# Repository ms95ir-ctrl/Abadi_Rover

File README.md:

# Abadi Rover

Two robots, one shared motherboard. Each robot has its own files, so they do not get mixed up.

| | Robot | Where its files are | Status |
|---|---|---|---|
| **Abadi Rover 1** | The tracked rover: ELEGOO tracked chassis, Raspberry Pi 5, ESP32-S3 motherboard, camera, audio. | The files at the **top level** of this repository: [`plan.md`](plan.md) (the locked build plan), [`wiring.md`](wiring.md), [`HANDOVER.md`](HANDOVER.md), [`wiring-map.png`](wiring-map.png), [`wiring-map.svg`](wiring-map.svg), [`wiring-map-unoq.png`](wiring-map-unoq.png), [`relay-wiring.png`](relay-wiring.png), [`relay-wiring.svg`](relay-wiring.svg) | In progress (still being built) |
| **Abadi Rover 2** | The telepresence robot: round base, 7 inch screen and camera on a pan/tilt head, Raspberry Pi 5 for video calls. It will be built abroad, so the owner can call family and drive the robot around the house from Germany. | The folder [`abadi-rover-2/`](abadi-rover-2/) (start with its [`README.md`](abadi-rover-2/README.md)) | First design draft |
| **Shared motherboard** | The 100 x 100 mm ESP32-S3 board (KiCad 7, 2 layers) used by both robots. The owner reports that five boards were ordered, for five different robots. | The folder [`pcb/kicad/`](pcb/kicad/) (start with its [`README.md`](pcb/kicad/README.md); locked pin table: [`pin-table.md`](pcb/kicad/pin-table.md)) | v5 designed and checked. Order only after the paper test-fit in `pcb/kicad/README.md` passes. If the owner has already ordered, he must confirm the ordered files are v5 (they must match `pin-table.md`) |

## Rules that keep the two robots apart

- Robot 1's files stay where they are. Other tools (for example Cursor) read `plan.md` at the top level, so they are not moved.
- Robot 2 is written only inside `abadi-rover-2/`. It does not change `plan.md`, `wiring.md`, `HANDOVER.md` or anything else of robot 1.
- The motherboard folder is shared. Its pin table and power design are **locked**; a change needs the owner's explicit approval, because both robots depend on it.
- One stage at a time. A robot's code is only written for the stage that is being built and tested.

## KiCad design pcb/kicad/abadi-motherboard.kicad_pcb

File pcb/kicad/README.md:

# Robot motherboard - routed draft v5, 2 layers, 100 x 100 mm

**Status: DRAFT. Do not order yet.** v5 is built from the owner's paper test-fits, photos and readings of the real modules. It is fully
routed and passes every check I could run on the files. Before ordering: print the new template, check the two DRV8833 modules
and a screen cable against it (see "Still to confirm"), and read the independent-review notes below.

## What changed in v5

- **DRV8833 (HW-627) footprints redrawn: two rows of 6 holes**, as read from the real module. Top row, left to right: IN1 IN2 VCC GND IN3 IN4
  (VCC is the motor supply = the battery). Bottom row, the side with the white plug: EEP OUT1 OUT2 OUT3 OUT4 ULT (EEP and ULT are not used).
  The pin names are printed beside the holes. M1 = DRV A OUT1+OUT2, M2 = DRV A OUT3+OUT4, M3/M4 = the same for DRV B.
  Note: the owner's own wording listed the IN row as "IN4 IN3 GND VCC IN2 IN1"; I drew it in the opposite direction (IN1 IN2 VCC GND IN3 IN4),
  assuming each row was read upright from its own edge, which also matches the seller's pin table. A thick silkscreen bar marks the plug side.
- **Screen headers follow the screens' own order:** CS DC RST SDA SCL VCC GND (pin 1 = square pad = CS).
- **Capacitor ratings are printed on the board** (C1 470uF 16V, C2 100uF 10V, C3/C4 100n) and listed in `parts-list.md`.
- **Plotted board size is exactly 100.0 x 100.0 mm** (the outline line used to add 0.1 mm). The fab cuts along the middle of that 0.1 mm line, so the finished board is
  99.9 x 99.9 mm; the mounting holes do not move. This keeps it inside the cheapest price tier.
- **30 ground stitching vias** tie the top and bottom ground pours together (the farthest spot from a tie is now about 12 mm instead of 37 mm).
- The relay/sonar and I2C/UART header strips have 3.0 mm between neighbouring headers (the screen and SPARE strip at the top is tighter: use slim plugs there),
  the labels on the top header row moved away from the pads and the board edge, version text says v5.
- New files: `shopping-list.md` (everything to buy, including the parts that are not on the board) and `stitch_ground.py`.

Carried over from v4: four 5.08 mm left-edge screw terminals (SERVO 5V IN, BATT IN, CLEAN 5V IN, 3.3V IN), the POWER OUT header
(2 x clean 5 V, 2 x 3.3 V from the 3.3 V buck, 4 x GND), 2-pin JST-style motor spots M1-M4, no series resistors on the relay inputs
(3 V relay modules have their own input circuit), sonar echo dividers 1k/2k (ESP32-S3 pins are not 5 V tolerant).

## How to wire the power

The three bucks are separate modules (not on the board). Each one has an input pair (IN+ / IN-) and an output pair (OUT+ / OUT-).

```
battery pack -> BMS -> main switch -> splice (lever connectors, one for + and one for -; 6-way if the Pi buck is used), one FUSE per branch:
     |-> board terminal BATT IN        (motors; 5 A slow-blow, 6 A at most: the board's 2 mm battery copper is a roughly 6 A design)
     |-> servo buck IN+/IN-  (5 A fuse)  its OUT+/OUT- go to the board terminal SERVO 5V IN   (-> PCA9685 V+ pin)
     |-> clean 5V buck IN+/IN-  (2 A fuse)  its OUT+/OUT- go to the board terminal CLEAN 5V IN   (-> ESP32 5V pin via diode D1, both sonars, POWER OUT 5V pins)
     |-> 3.3V buck IN+/IN-  (2 A fuse)   its OUT+/OUT- go to the board terminal 3.3V IN       (-> relays, screens, POWER OUT 3V3 pins)
     '-> (optional) Raspberry Pi 5: own 5.1 V buck, 5 A fuse, straight to the Pi. It does not touch the board.
```

**+** is the square pad of each terminal. All **-** terminals and all GND pins are one common ground. Before connecting a buck to the board,
power it from the battery alone and set its output with a multimeter (servo buck 5.0 V, clean buck 5.0 V, 3.3 V buck 3.3 V).
The board has no fuse and no reverse-polarity protection. Each POWER OUT rail (two pins) shares one 0.5 mm track: the copper is good for about 2 A,
but the buck also feeds the ESP32, sonars, relays and screens, so plan on about **1 A** for your own sensors. Do not connect one sensor to both the
POWER OUT 3V3 pins (3.3 V buck) and the I2C / SPARE 3V3 pins (the ESP32's own pin): they are different sources. The ESP32
reaches 5 V through D1 and its own diode, so check on first power-up that its 3.3 V pin stays at 3.2 V or higher with Wi-Fi transmitting.

## What is here

| File | What it is |
|---|---|
| `board-top.png` | what the finished board will look like from above |
| `board-copper.png` | both copper layers |
| `fit-template-1to1.pdf` | **print at 100 % / actual size** and lay your modules on it (the 50 mm ruler must measure 50 mm) |
| `abadi-motherboard.kicad_pcb` + `.kicad_pro` | the board in KiCad 7 (keep both files together: the .kicad_pro holds the design rules) |
| `gerber/` and `abadi-motherboard-2layer-gerber.zip` | the fab files (this zip is what you upload to the PCB maker) |
| `pin-table.md` | which ESP32 pin carries which signal, and every connector's pin order |
| `parts-list.md` | what to buy for every footprint, with ratings |
| `shopping-list.md` | everything to buy, on and off the board, plus the first power-up steps |
| `power-wiring.png` / `.svg` | wiring diagram: cells, BMS, charger, splice, fuses, bucks, motherboard terminals |
| `battery-wiring.png` / `.svg` | wiring diagram for the battery only: 2 cells, the BMS (P+ P- / B+ BM B-) and the IP2326 USB-C charger board |
| `reports/` | KiCad's design-rule report and my independent check of the Gerber files |

## Still to confirm (paper test-fit with the new template)

1. **DRV8833 row gap.** The two rows of holes are drawn 16.0 mm apart (estimated from a photo). Measure the real distance between the
   centres of the two rows and tell me; it moves by a fraction of a millimetre at most, but the pins must fall in the holes.
2. **DRV8833 alignment.** I assumed EEP sits directly across from IN1 (and ULT across from IN4), which matches the seller's pin table.
   Check on the real module. If EEP is across from IN4, the two rows are mirrored and I must redraw them.
3. **Screen cable.** Pin 1 of each screen header is CS. Check against the pin labels printed on your screen.
4. **Compare every printed name with the module's own labels, pin by pin, not just whether the pins fall in the holes.** With the white plug
   toward the bottom edge, the IN row (top) must read IN1 IN2 VCC GND IN3 IN4 from the left, and the module's VCC must be the pin over the
   printed "VCC". VCC and GND are next to each other: a mirrored module would put the battery on its ground pin.
5. On the real module, with a meter: is EEP already tied high? If the motors do not run, EEP (sleep) needs a wire to 3.3 V. The owner says EEP and ULT are not needed.
   The PCA9685's OE pin is left open (the module normally pulls it low).
6. Also lay down the ESP32 (USB-C to the right), PCA9685 (header at the left end), gyro, a sonar cable and a screw terminal.

## What was checked

- KiCad design-rule check: **0 errors, 0 unconnected pads.** (38 notes say the footprints are not from a KiCad library; they are
  drawn in code, so that is expected and harmless.)
- A separate checker I wrote reads only the exported Gerber and drill files, rebuilds which copper touches which, and compares with the
  intended nets: **0 shorts, 0 opens**, all 211 plated holes (pads and vias) match the design (the 4 mounting holes are in a separate unplated file).
  Smallest copper gap 0.152 mm, narrowest track 0.25 mm, smallest drill 0.30 mm, copper at least 0.5 mm from the edge.
- Independent reviewers (separate agents, v4 design): netlist and pin tables (0 mismatches), grounding (all 32 ground pads are one
  connected piece; motor-return resistance about 1 mOhm), fab files, silkscreen, documents, electrical safety. They found the DRV8833 and
  screen mismatches, the missing capacitor ratings and the 100.1 mm size; those are fixed here. The v5 changes (DRV, screens,
  stitching vias) have been checked by KiCad and the Gerber audit; see `reports/` for the latest numbers.

## What is NOT checked

1. **Module pin orders** other than those listed above as read from the owner's modules: the relay (VCC IN GND), sonar (VCC TRIG ECHO GND),
   GY-521 and PCA9685 match the owner's photos and the usual orders; the I2C and UART headers have no module behind them.
2. The ESP32 pin map is my optimized proposal. `plan.md` and `wiring.md` are **not** updated, and their locked pin table still
   describes the old build. SPARE IO pins 3, 45, 46 are boot-strapping pins (46 is input-only) and 38/48 drive the devkit's RGB LED.
3. No schematic and no electrical simulation. The netlist lives in `build_board.py`.
4. Current limits (1 oz copper): VBAT copper is 2.0 mm (a roughly 6 A design), SERVO5 1.5 mm, motor traces 1.0 mm, CLEAN5 / RAILC 0.5 mm. A PCA9685 header
   pin is good for roughly 2-3 A: for big servos also use the module's own screw terminal. Nothing is tested under load.
5. **The ESP32 board only fits one way round:** the USB-C end toward the **right** edge, the antenna toward the left (marked on the board,
   with the two USB-C sockets drawn). Turned around, its 3V3 pins land on the GND pins. The first hole of each row (square pad) is the antenna end.
6. The PCA9685 has no mounting hole: it sits on its header pins. **A DRV8833 module pushed in 180 degrees rotated fits the holes** (the pattern is
   point-symmetric) and would put battery voltage on ESP32 pins GPIO1 / GPIO16 and its outputs on GND and VBAT. Check the thick plug-side bar and
   "white plug v" before every insertion, and insert the DRV modules only after the first power-up test.
   The UART header is the ESP32's console UART (GPIO43/44): it receives boot text, so unplug it while flashing.
7. The power-track widths (VBAT 2.0, SERVO5 1.5, motors 1.0, 5 V / 3.3 V 0.5 mm) exist only in the routed copper, not as rules in the .kicad_pro;
   keep them if you edit the board.
8. The I2C bus has no pull-up resistors on the board; it relies on the PCA9685 and GY-521 modules' own.

## Paper test-fit (10 minutes, free)

Print `fit-template-1to1.pdf` at 100 %. Check the 50 mm ruler. Lay each module on the sheet: its pins should fall in the holes, its body
inside the printed outline. Check polarity marks on the terminals (+ is the square pad) against your wiring. Tell me anything that does not line up.

## Ordering (when the test-fit passes)

JLCPCB, 2 layers, 100 x 100 mm, 5 pieces, 1.6 mm, any solder-mask colour, bare board only (no assembly); HASL with lead is the cheapest
finish, lead-free costs a little more. Upload `abadi-motherboard-2layer-gerber.zip` as it is. JLCPCB's help page lists $2 for five 2-layer
boards up to 10 x 10 cm; shipping and German VAT are added at checkout. The preview must show 100 x 100 mm; the final price appears on their
quote page before you pay. The soldered parts are all through-hole, so assembly by the fab is not an option; buy the parts (see `shopping-list.md`).

## How it was made (to redo it after a change)

```
python3 build_board.py board.kicad_pcb --layers 2 --fine --pinmap     # parts, nets, outline, pours
python3 route_board.py board.kicad_pcb routed.kicad_pcb freerouting-2.0.1.jar 80
python3 stitch_ground.py routed.kicad_pcb stitched.kicad_pcb 30        # ground stitching vias (copy the .kicad_pro next to each file)
python3 finish_board.py stitched.kicad_pcb final.kicad_pcb              # silk size, pour refill, DRC report
kicad-cli pcb export gerbers ... ; kicad-cli pcb export drill ...        # fab files
python3 dump_board.py final.kicad_pcb design.json
python3 audit_kicad_gerbers.py gerber design.json                       # independent check
python3 render_board.py gerber pics ; python3 make_docs.py final.kicad_pcb docs   # pictures, template PDF, pin table, parts list
```

The delivered board has two small hand edits after routing (the 30 stitching vias, and a 0.14 mm dogleg in the RAILC trunk below RLY1H pad 1 to remove
a 0.03 mm slit), plus the silkscreen tweaks that are also in `build_board.py`. The auto-router gives a different result each time the board is rebuilt (even with the file name changed). Rebuild and re-route, or change
`HDR_GAP` slightly, until the report shows 0 unconnected and the audit shows no copper gap or slit below 0.14 mm. `assign_pins.py` re-optimizes which
ESP32 pin drives which signal. Needs KiCad 7 (python3 `pcbnew`), Java 21 and
[Freerouting 2.0.1](https://github.com/freerouting/freerouting/releases/tag/v2.0.1). The earlier `pcb/` files from Cursor (the 4-layer
105 x 84 mm draft) are superseded by this folder.

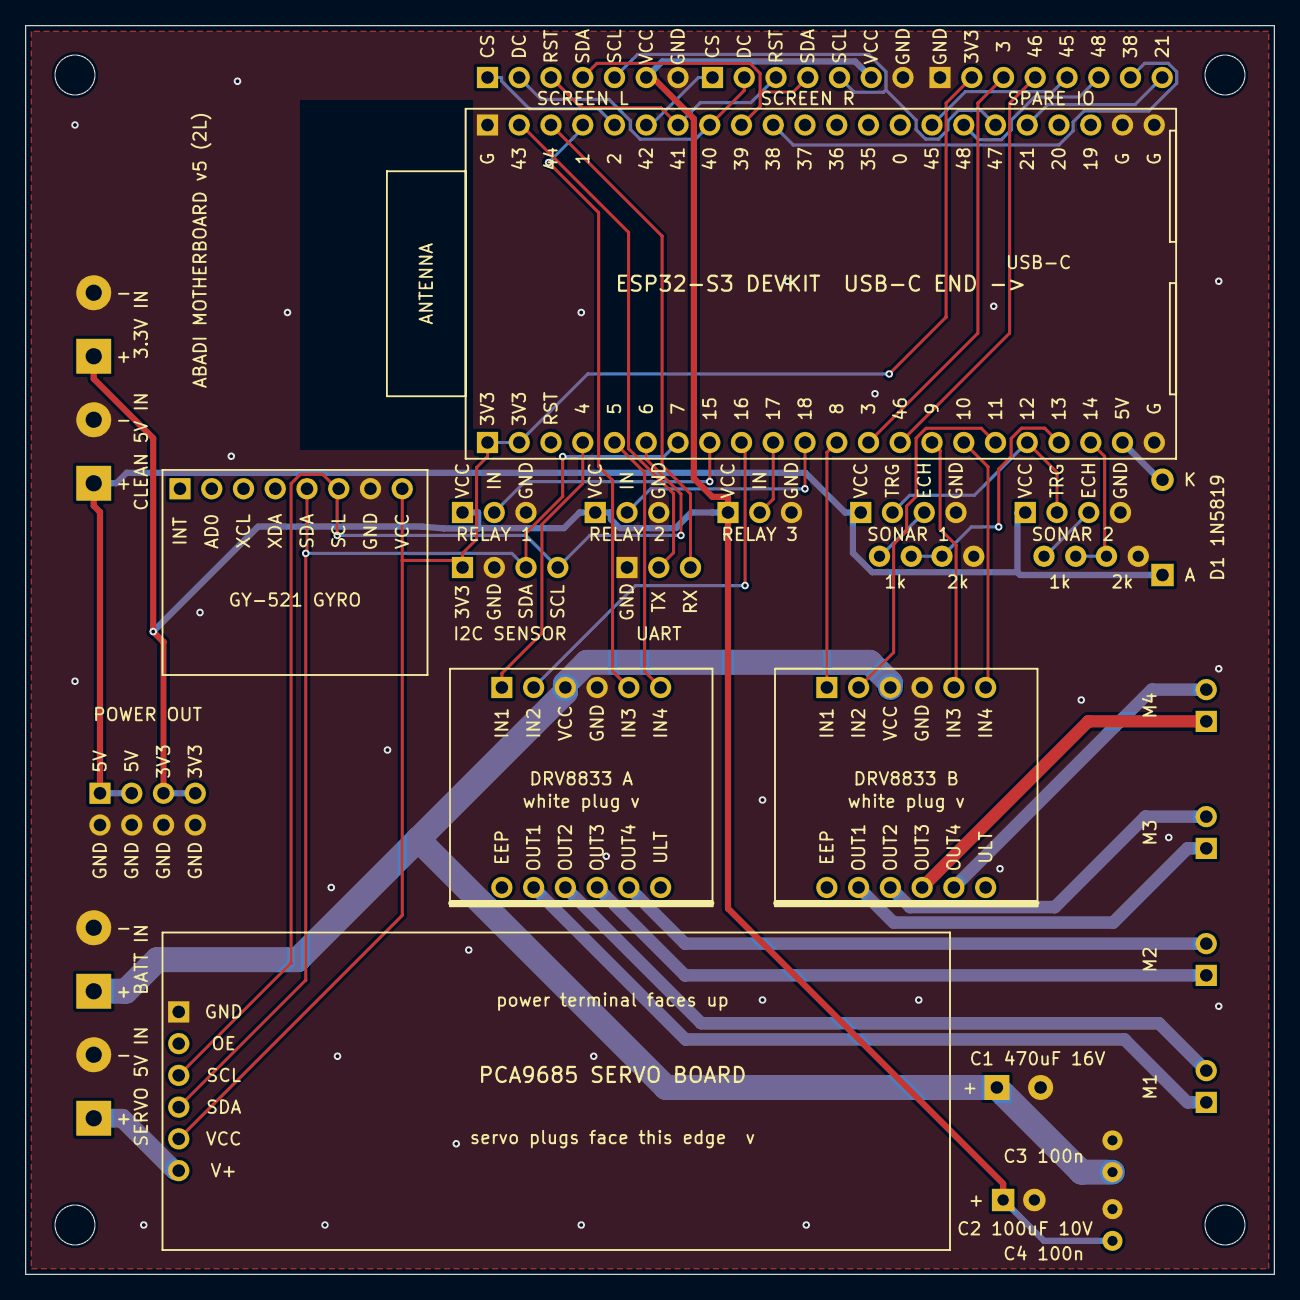
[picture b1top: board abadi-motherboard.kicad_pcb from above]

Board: 2 copper layers, 99.9 x 99.9 mm, 38 parts (0 on the bottom side), 47 nets.

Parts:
C1: 470uF pack; FP_C1
C2: 100uF 3V3; FP_C2
C3: 100nF pack; FP_C3
C4: 100nF 3V3; FP_C4
D1: Schottky 1N5819; FP_D1
DRVA: DRV8833 A; FP_DRVA
DRVB: DRV8833 B; FP_DRVB
GYRO: GY-521 (INT AD0 XCL XDA SDA SCL GND VCC); FP_GYRO
H1, H2, H3, H4: MOUNT_M3
I2C: I2C SENSOR; FP_I2C
J1: ESP32-S3 row 1 (3V3 RST 4 5 ...); FP_J1
J3: ESP32-S3 row 2 (GND TX RX 1 2 ...); FP_J3
PCA: PCA9685 header (GND OE SCL SDA VCC V+); FP_PCA
PWR: POWER OUT (5V 5V 3V3 3V3 / GND x4); FP_PWR
RD1a: 1k; FP_RD1a
RD1b: 2k; FP_RD1b
RD2a: 1k; FP_RD2a
RD2b: 2k; FP_RD2b
RLY1H: RELAY 1; FP_RLY1H
RLY2H: RELAY 2; FP_RLY2H
RLY3H: RELAY 3; FP_RLY3H
SCR_L: SCREEN L; FP_SCR_L
SCR_R: SCREEN R; FP_SCR_R
SON1: SONAR 1; FP_SON1
SON2: SONAR 2; FP_SON2
SPARE: SPARE IO; FP_SPARE
TL0: SERVO 5V IN; FP_TL0
TL1: BATT IN; FP_TL1
TL2: CLEAN 5V IN; FP_TL2
TL3: 3.3V IN; FP_TL3
TM1: MOTOR 1 (2-pin JST); FP_TM1
TM2: MOTOR 2 (2-pin JST); FP_TM2
TM3: MOTOR 3 (2-pin JST); FP_TM3
TM4: MOTOR 4 (2-pin JST); FP_TM4
UART: UART; FP_UART

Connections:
CLEAN5: D1.1, PWR.1, PWR.2, SON1.1, SON2.1, TL2.1
CS_L: J3.5, SCR_L.1
CS_R: J3.6, SCR_R.1
ECHO1_3V: J1.19, RD1a.2, RD1b.1
ECHO1_5V: RD1a.1, SON1.3
ECHO2_3V: J1.20, RD2a.2, RD2b.1
ECHO2_5V: RD2a.1, SON2.3
ESP3V3: GYRO.8, I2C.1, J1.1, J1.2, PCA.5, SPARE.2
ESP5V: D1.2, J1.21
GND: C1.2, C2.2, C3.2, C4.2, DRVA.4, DRVB.4, GYRO.7, I2C.2, J1.22, J3.1, J3.21, J3.22, PCA.1, PWR.5, PWR.6, PWR.7, PWR.8, RD1b.2, RD2b.2, RLY1H.3, RLY2H.3, RLY3H.3, SCR_L.7, SCR_R.7, SON1.4, SON2.4, SPARE.1, TL0.2, TL1.2, TL2.2, TL3.2, UART.1
IN1A: DRVA.1, J1.4
IN1B: DRVB.1, J1.12
IN2A: DRVA.2, J1.9
IN2B: DRVB.2, J1.17
IN3A: DRVA.5, J3.4
IN3B: DRVB.5, J1.15
IN4A: DRVA.6, J1.5
IN4B: DRVB.6, J1.16
LCD_DC: J3.8, SCR_L.2, SCR_R.2
LCD_RST: J3.7, SCR_L.3, SCR_R.3
M1A: DRVA.8, TM1.1
M1B: DRVA.9, TM1.2
M2A: DRVA.10, TM2.1
M2B: DRVA.11, TM2.2
M3A: DRVB.8, TM3.1
M3B: DRVB.9, TM3.2
M4A: DRVB.10, TM4.1
M4B: DRVB.11, TM4.2
MOSI: J3.9, SCR_L.4, SCR_R.4
RAILC: C2.1, C4.1, PWR.3, PWR.4, RLY1H.1, RLY2H.1, RLY3H.1, SCR_L.6, SCR_R.6, TL3.1
RLY1: J1.8, RLY1H.2
RLY2: J1.11, RLY2H.2
RLY3: J1.10, RLY3H.2
SCK: J3.17, SCR_L.5, SCR_R.5
SCL: GYRO.6, I2C.4, J1.6, PCA.3
SDA: GYRO.5, I2C.3, J1.7, PCA.4
SERVO5: PCA.6, TL0.1
SPARE3: J1.13, SPARE.3
SPARE21: J3.18, SPARE.8
SPARE38: J3.10, SPARE.7
SPARE45: J3.15, SPARE.5
SPARE46: J1.14, SPARE.4
SPARE48: J3.16, SPARE.6
TRIG: J1.18, SON1.2, SON2.2
UART_RX: J3.3, UART.3
UART_TX: J3.2, UART.2
VBAT: C1.1, C3.1, DRVA.3, DRVB.3, TL1.1

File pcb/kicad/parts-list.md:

# Parts list (generated from the board file)

| Qty | Item | Pads | Refs |
|---|---|---|---|
| 1 | 470 uF electrolytic capacitor, 16 V or higher (25 V is fine), radial, 3.5 mm lead spacing; long leg / no stripe = + (square pad) | 2 | C1 |
| 1 | 100 uF electrolytic capacitor, 10 V or higher, radial, 2.5 mm lead spacing; long leg / no stripe = + (square pad) | 2 | C2 |
| 1 | 100 nF ceramic capacitor (marked 104), 16 V or higher, 2.54 mm lead spacing, no polarity | 2 | C3 |
| 1 | 100 nF ceramic capacitor (marked 104), 16 V or higher, 2.54 mm lead spacing, no polarity | 2 | C4 |
| 1 | 1N5819 Schottky diode; the stripe end = K, goes to the hole marked K | 2 | D1 |
| 1 | two 1x6 female sockets, 2.54 mm (or solder the module's pins straight in) | 12 | DRVA |
| 1 | two 1x6 female sockets, 2.54 mm (or solder the module's pins straight in) | 12 | DRVB |
| 1 | 1x8 female socket, 2.54 mm | 8 | GYRO |
| 4 | M3 mounting hole (screw + nut), 3.2 mm | 1 | H1, H2, H3, H4 |
| 1 | 4-pin 2.54 mm male header or JST-XH socket (I2C SENSOR) | 4 | I2C |
| 1 | 22-pin female socket, 2.54 mm (the ESP32-S3 devkit's pins plug in) | 22 | J1 |
| 1 | 22-pin female socket, 2.54 mm (the ESP32-S3 devkit's pins plug in) | 22 | J3 |
| 1 | 1x6 pin header (pins down, plastic on the module's underside) plus a 1x6 socket on the board, or solder straight in | 6 | PCA |
| 1 | 2x4 pin header, 2.54 mm | 8 | PWR |
| 2 | 1 kOhm resistor, 1/4 W, stands upright | 2 | RD1a, RD2a |
| 2 | 2 kOhm resistor, 1/4 W, stands upright | 2 | RD1b, RD2b |
| 1 | 3-pin 2.54 mm male header or JST-XH socket (RELAY 1) | 3 | RLY1H |
| 1 | 3-pin 2.54 mm male header or JST-XH socket (RELAY 2) | 3 | RLY2H |
| 1 | 3-pin 2.54 mm male header or JST-XH socket (RELAY 3) | 3 | RLY3H |
| 1 | 7-pin 2.54 mm male header or JST-XH socket (SCREEN L) | 7 | SCR_L |
| 1 | 7-pin 2.54 mm male header or JST-XH socket (SCREEN R) | 7 | SCR_R |
| 1 | 4-pin 2.54 mm male header or JST-XH socket (SONAR 1) | 4 | SON1 |
| 1 | 4-pin 2.54 mm male header or JST-XH socket (SONAR 2) | 4 | SON2 |
| 1 | 8-pin 2.54 mm male header or JST-XH socket (SPARE IO) | 8 | SPARE |
| 1 | screw terminal, 2-pole, 5.08 mm pitch (hole 1.3 mm) | 2 | TL0 |
| 1 | screw terminal, 2-pole, 5.08 mm pitch (hole 1.3 mm) | 2 | TL1 |
| 1 | screw terminal, 2-pole, 5.08 mm pitch (hole 1.3 mm) | 2 | TL2 |
| 1 | screw terminal, 2-pole, 5.08 mm pitch (hole 1.3 mm) | 2 | TL3 |
| 1 | 2-pin 2.54 mm header or JST socket for the motor plug | 2 | TM1 |
| 1 | 2-pin 2.54 mm header or JST socket for the motor plug | 2 | TM2 |
| 1 | 2-pin 2.54 mm header or JST socket for the motor plug | 2 | TM3 |
| 1 | 2-pin 2.54 mm header or JST socket for the motor plug | 2 | TM4 |
| 1 | 3-pin 2.54 mm male header or JST-XH socket (UART) | 3 | UART |

Cable ports (relay, sonar, screen, I2C, UART, SPARE IO): standard 2.54 mm male pin headers, or JST-XH sockets (2.5 mm pitch; the owner's plugs fit this spacing). Power outputs and ground on the POWER OUT header: about 2 A per rail at most. The two resistors per sonar stand upright (holes 2.54 mm apart); D1 lies flat (holes 7.62 mm apart). See shopping-list.md for the parts that are not on the board (bucks, BMS, charger, fuses, connectors).

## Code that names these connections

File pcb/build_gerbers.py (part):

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
    esp = place("ESP32-S3", [
        ("GND", None),
        ("GPIO4", "IN1A"), ("GPIO5", "IN2A"), ("GPIO6", "IN3A"), ("GPIO7", "IN4A"),
        ("GPIO15", "IN1B"), ("GPIO16", "IN2B"), ("GPIO17", "IN3B"), ("GPIO18", "IN4B"),
        ("GPIO8", "SDA"), ("GPIO9", "SCL"),
        ("GPIO1", "RLY1"), ("GPIO2", "RLY2"), ("GPIO38", "RLY3"), ("GPIO39", "RLY4"),
        ("GPIO13", "CSL"), ("GPIO14", "CSR"), ("GPIO21", "DC"), ("GPIO10", "RST"),
        ("GPIO11", "MOSI"), ("GPIO12", "SCK"),
        ("GPIO41", "TRIG"), ("GPIO42", "ECHO3"),
        ("GPIO40", "SPARE"),
        ("3V3", "ESP3V3"),
        ("GND", None),
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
